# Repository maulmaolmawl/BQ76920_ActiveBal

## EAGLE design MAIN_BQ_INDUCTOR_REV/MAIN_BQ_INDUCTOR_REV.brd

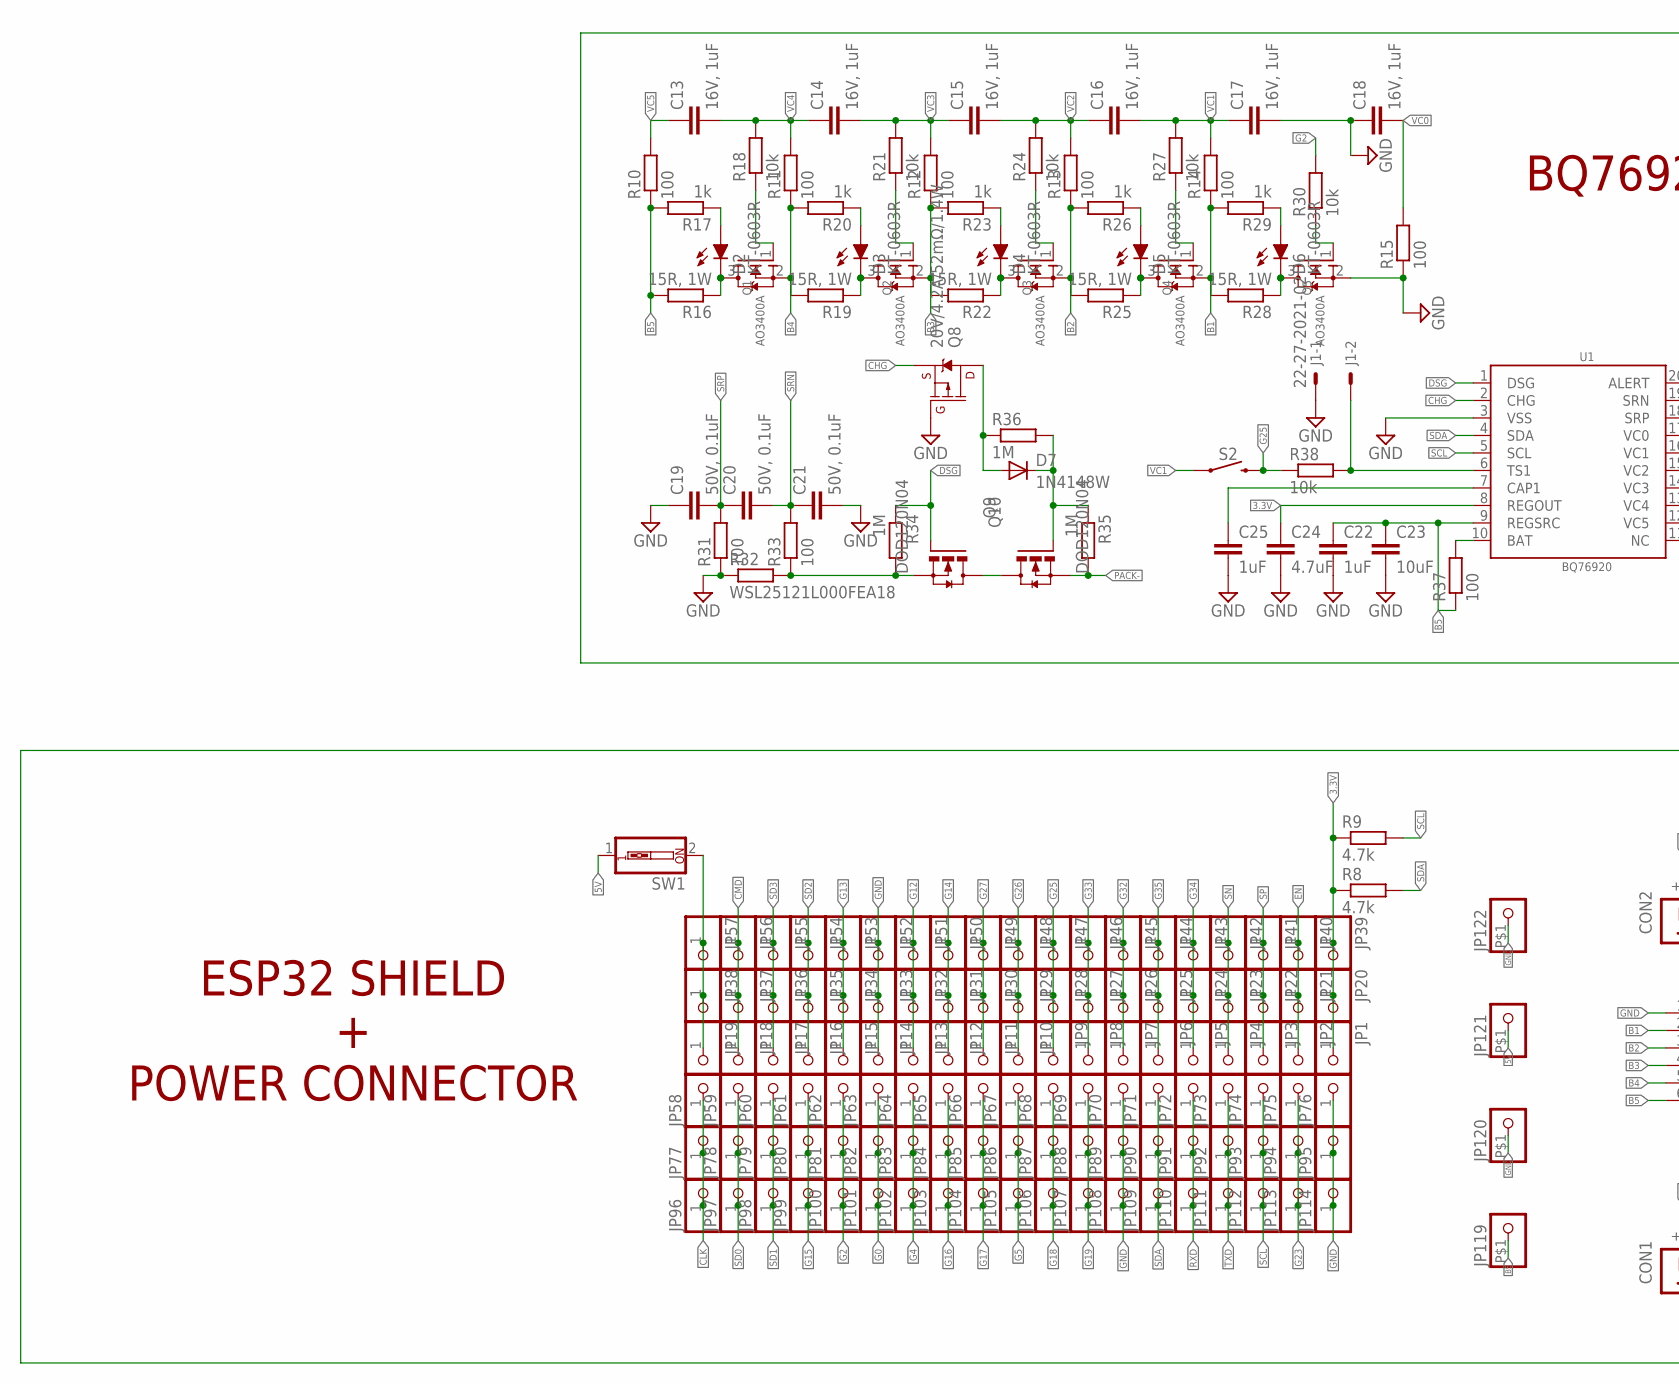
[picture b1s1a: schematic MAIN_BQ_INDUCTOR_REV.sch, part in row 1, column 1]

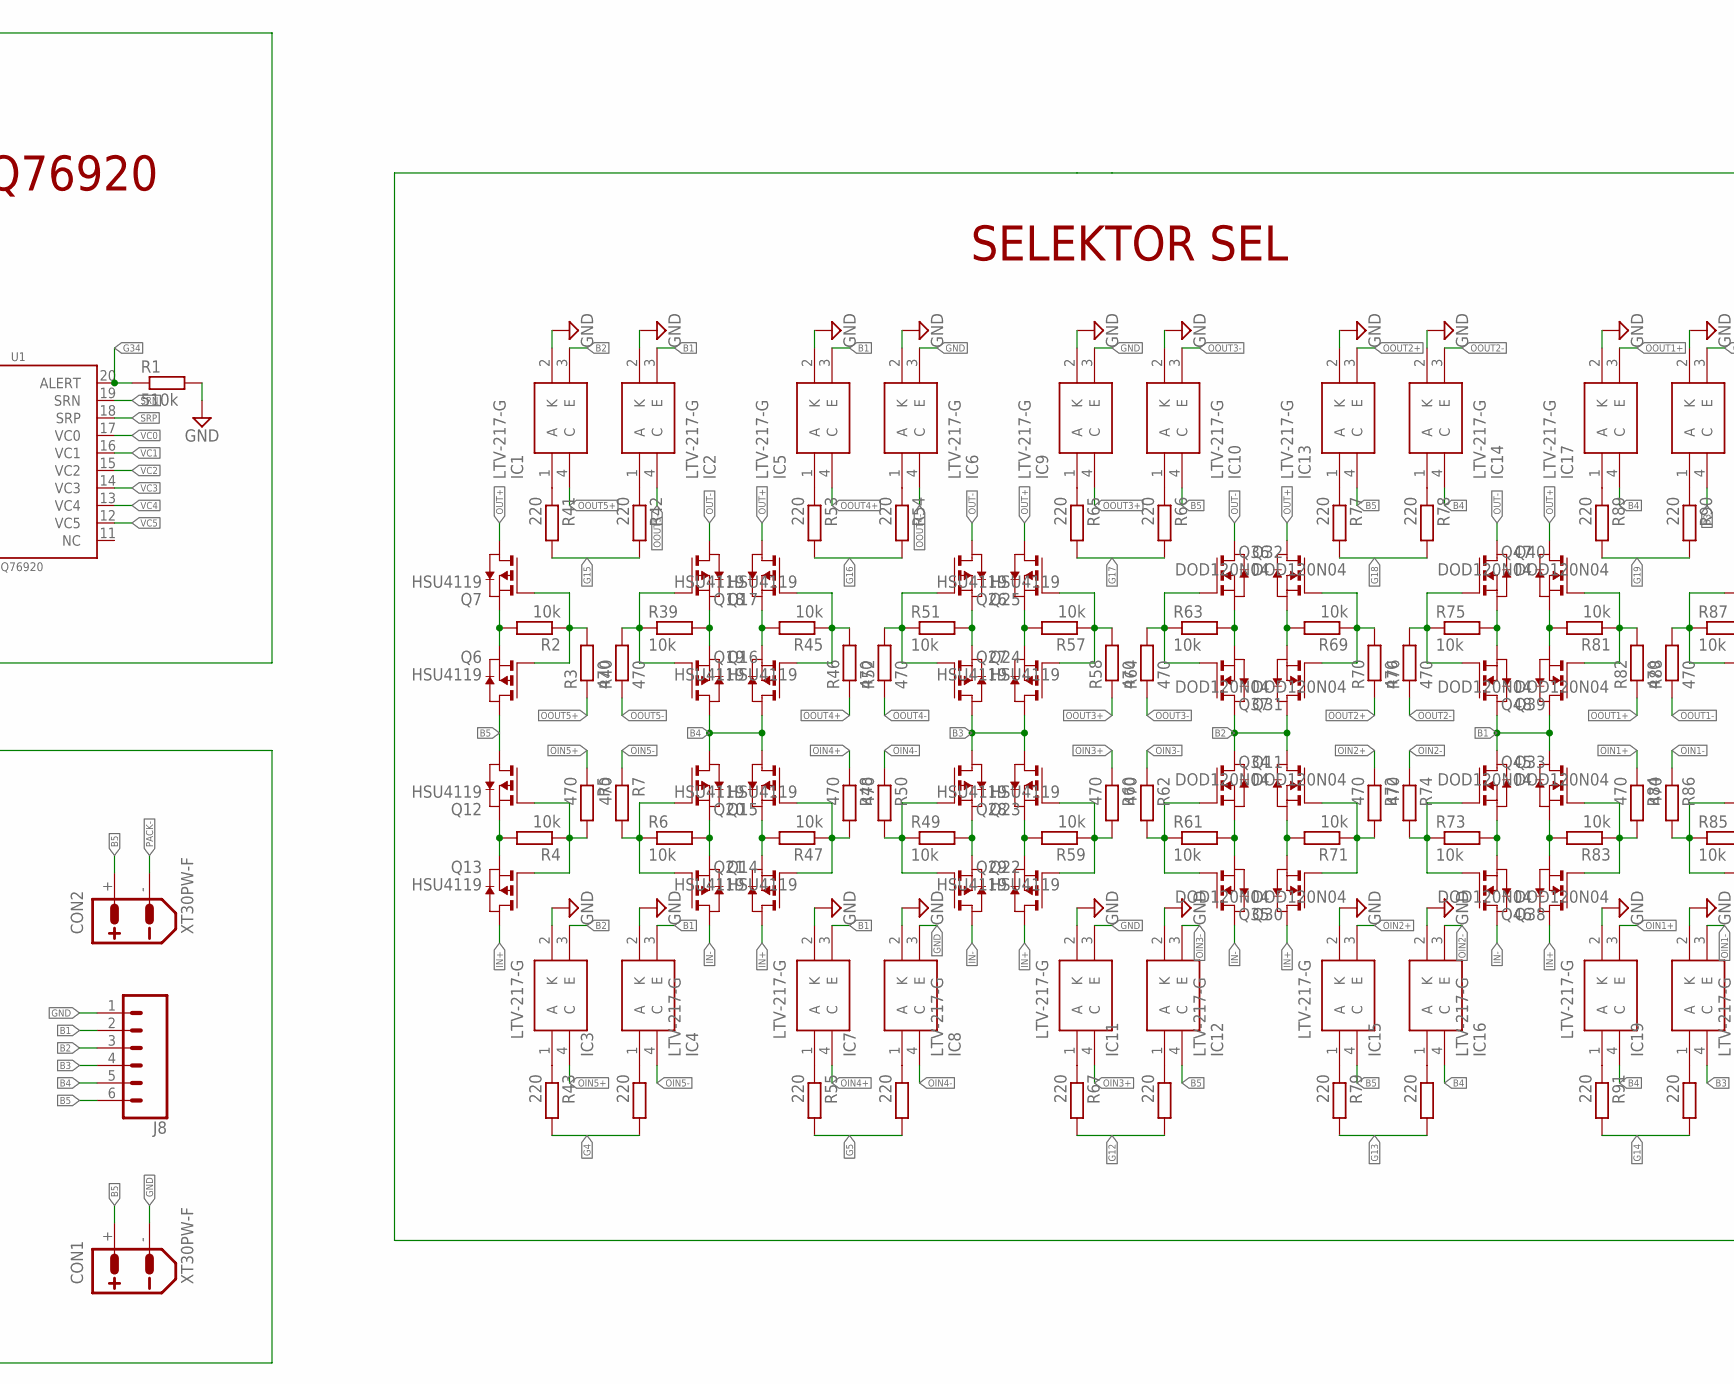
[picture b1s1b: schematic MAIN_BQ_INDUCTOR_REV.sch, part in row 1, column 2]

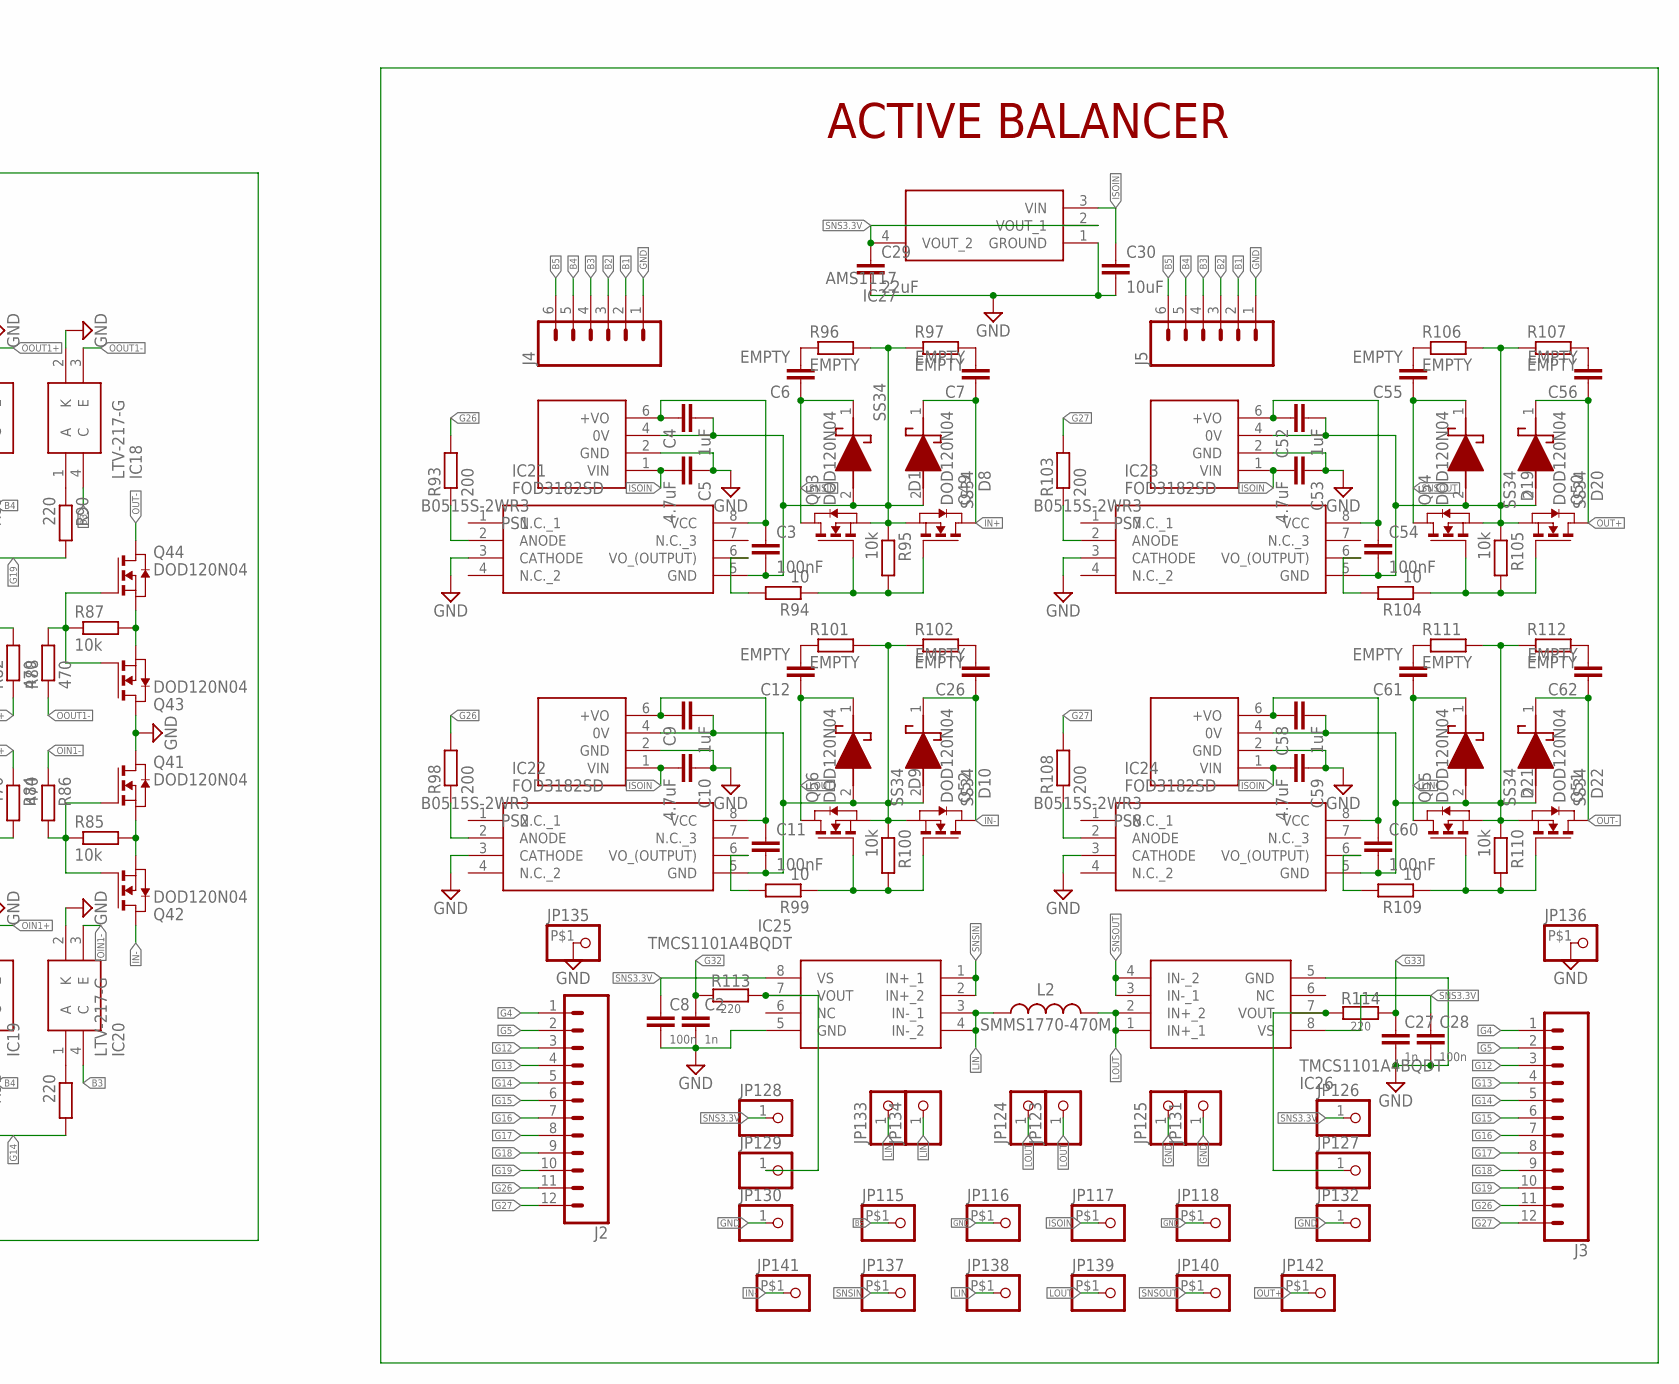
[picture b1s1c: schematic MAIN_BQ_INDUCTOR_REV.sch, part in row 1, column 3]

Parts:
C2, C27: 1n; C0805
C3, C11, C54, C60: 100nF; C0805
C4, C9, C52, C58: 1uF; C1206
C5, C10, C53, C59: 4.7uF; C1206
C6, C7, C12, C26, C55, C56, C61, C62: EMPTY; C1206
C8, C28: 100n; C0805
C13, C14, C15, C16, C17, C18: 16V, 1uF; C0805
C19, C20, C21: 50V, 0.1uF; C0603
C22, C25: 1uF; C0805
C23: 10uF; C1206
C24: 4.7uF; C0805
C29: 22uF; C0805
C30: 10uF; C0805
CON1, CON2: XT30PW-F
D1, D8, D9, D10, D19, D20, D21, D22: SS34; DIOM6959X262N
D2, D3, D4, D5, D6: KT-0603R; LED_CHIP-LED0603MP
D7: 1N4148W; SOD-123
IC1, IC2, IC3, IC4, IC5, IC6, IC7, IC8, IC9, IC10, IC11, IC12, IC13, IC14, IC15, IC16, IC17, IC18, IC19, IC20: LTV-217-G; LTV217G
IC21, IC22, IC23, IC24: FOD3182SD; SOP254P1000X400-8N
IC25, IC26: TMCS1101A4BQDT; SOIC127P600X175-8N
IC27: AMS1117; SOT229P700X180-4N
J1: 22-27-2021-02; 6410-02
J2, J3: CONN_12; 1X12
J4, J5, J8: CONN_06LONGPADS; 1X06_LONGPADS
JP1, JP2, JP3, JP4, JP5, JP6, JP7, JP8, JP9, JP10, JP11, JP12, JP13, JP14, JP15, JP16, JP17, JP18, JP19, JP20, JP21, JP22, JP23, JP24, JP25, JP26, JP27, JP28, JP29, JP30, JP31, JP32, JP33, JP34, JP35, JP36, JP37, JP38, JP39, JP40, JP41, JP42, JP43, JP44, JP45, JP46, JP47, JP48, JP49, JP50, JP51, JP52, JP53, JP54, JP55, JP56, JP57, JP58, JP59, JP60, JP61, JP62, JP63, JP64, JP65, JP66, JP67, JP68, JP69, JP70, JP71, JP72, JP73, JP74, JP75, JP76, JP77, JP78, JP79, JP80, JP81, JP82, JP83, JP84, JP85, JP86, JP87, JP88, JP89, JP90, JP91, JP92, JP93, JP94, JP95, JP96, JP97, JP98, JP99, JP100, JP101, JP102, JP103, JP104, JP105, JP106, JP107, JP108, JP109, JP110, JP111, JP112, JP113, JP114, JP123, JP124, JP125, JP126, JP127, JP128, JP129, JP130, JP131, JP132, JP133, JP134: PINHD-1X1; 1X01
JP115, JP116, JP117, JP118, JP119, JP120, JP121, JP122, JP135, JP136, JP137, JP138, JP139, JP140, JP141, JP142: PINHD-1X1-BIGPOGO; 1X1-BIGPOGO
L2: SMMS1770-470M; PA4344-17X17
PS1, PS2, PS7, PS8: B0515S-2WR3; B1212S2WR3
Q1, Q2, Q3, Q4, Q5: AO3400A; SOT23
Q6, Q7, Q12, Q13, Q14, Q15, Q16, Q17, Q18, Q19, Q20, Q21, Q22, Q23, Q24, Q25, Q26, Q27, Q28, Q29: HSU4119; TO252
Q8: 20V/4.2A/52mΩ/1.4W; SOT23-3
Q9, Q10: DOD120N04; DPAK
Q11, Q30, Q31, Q32, Q33, Q34, Q35, Q36, Q37, Q38, Q39, Q40, Q41, Q42, Q43, Q44, Q45, Q46, Q47, Q48, Q49, Q50, Q51, Q52, Q53, Q54, Q55, Q56: DOD120N04; TO252
R1: 510k; R0603
R2, R4, R6, R39, R45, R47, R49, R51, R57, R59, R61, R63, R69, R71, R73, R75, R81, R83, R85, R87, R95, R100, R105, R110: 10k; R0805
R3, R5, R7, R40, R46, R48, R50, R52, R58, R60, R62, R64, R70, R72, R74, R76, R82, R84, R86, R88: 470; R0805
R8, R9: 4.7k; R0402
R10, R11, R12, R13, R14, R15, R37: 100; R1206
R16, R19, R22, R25, R28: 15R, 1W; R2512
R17, R20, R23, R26, R29: 1k; R0402
R18, R21, R24, R27, R30, R38: 10k; R0402
R31, R33: 100; R0805
R32: WSL25121L000FEA18; R2512
R34, R35, R36: 1M; R0805
R41, R42, R43, R44, R53, R54, R55, R56, R65, R66, R67, R68, R77, R78, R79, R80, R89, R90, R91, R92, R113, R114: 220; R0805
R93, R98, R103, R108: 200; R0805
R94, R99, R104, R109: 10; R1206
R96, R97, R101, R102, R106, R107, R111, R112: EMPTY; R1206
S2: MOMENTARY-SWITCH-SPST-SMD-5.2-TALL-REDUNDANT; TACTILE_SWITCH_SMD_5.2MM
SW1: SW_DIP-1; EDG-01
U1: BQ76920; TSSOP-20_4.4X6.5MM_PITCH0.65MM

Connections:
3.3V: C24.1, JP1.1, JP20.1, JP39.1, R8.1, R9.1, U1.8 (REGOUT)
5V: JP121.P$1, SW1.1
B1: IC2.3 (E), IC4.3 (E), IC5.3 (E), IC7.3 (E), J4.2, J5.2, J8.2, Q4.2 (S), Q33.D, Q39.D, Q45.D, Q48.D, R14.1, R28.2, R29.2
B2: IC1.3 (E), IC3.3 (E), J4.3, J5.3, J8.3, Q3.2 (S), Q11.D, Q31.D, Q34.D, Q37.D, R13.1, R25.2, R26.2
B3: IC18.4 (C), IC20.4 (C), J4.4, J5.4, J8.4, Q2.2 (S), Q23.D, Q24.D, Q27.D, Q28.D, R12.1, R22.2, R23.2
B4: IC14.4 (C), IC16.4 (C), IC17.4 (C), IC19.4 (C), J4.5, J5.5, J8.5, Q1.2 (S), Q15.D, Q16.D, Q19.D, Q20.D, R11.1, R19.2, R20.2
B5: C22.1, C23.1, CON1.+, CON2.+, IC10.4 (C), IC12.4 (C), IC13.4 (C), IC15.4 (C), J4.6, J5.6, J8.6, JP115.P$1, JP119.P$1, Q6.D, Q12.D, R10.1, R16.2, R17.2, R37.1, U1.9 (REGSRC)
CHG: Q8.2 (S), U1.2 (CHG)
CLK: JP58.1, JP77.1, JP96.1
CMD: JP18.1, JP37.1, JP56.1
DSG: Q9.1 (G), R34.1, U1.1 (DSG)
EN: JP2.1, JP21.1, JP40.1
G0: JP63.1, JP82.1, JP101.1
G2: JP62.1, JP81.1, JP100.1, R30.2
G4: J2.1, J3.1, JP64.1, JP83.1, JP102.1, R43.2, R44.2
G5: J2.2, J3.2, JP67.1, JP86.1, JP105.1, R55.2, R56.2
G12: J2.3, J3.3, JP13.1, JP32.1, JP51.1, R67.2, R68.2
G13: J2.4, J3.4, JP15.1, JP34.1, JP53.1, R79.2, R80.2
G14: J2.5, J3.5, JP12.1, JP31.1, JP50.1, R91.2, R92.2
G15: J2.6, J3.6, JP61.1, JP80.1, JP99.1, R41.2, R42.2
G16: J2.7, J3.7, JP65.1, JP84.1, JP103.1, R53.2, R54.2
G17: J2.8, J3.8, JP66.1, JP85.1, JP104.1, R65.2, R66.2
G18: J2.9, J3.9, JP68.1, JP87.1, JP106.1, R77.2, R78.2
G19: J2.10, J3.10, JP69.1, JP88.1, JP107.1, R89.2, R90.2
G23: JP75.1, JP94.1, JP113.1
G25: JP9.1, JP28.1, JP47.1, R38.1, S2.3 (2), S2.4 (2)
G26: J2.11, J3.11, JP10.1, JP29.1, JP48.1, R93.2, R98.2
G27: J2.12, J3.12, JP11.1, JP30.1, JP49.1, R103.2, R108.2
G32: C2.1, JP7.1, JP26.1, JP45.1, R113.1
G33: C27.1, JP8.1, JP27.1, JP46.1, R114.2
G34: JP5.1, JP24.1, JP43.1, R1.1, U1.20 (ALERT)
G35: JP6.1, JP25.1, JP44.1
GND: C2.2, C5.1, C8.2, C10.1, C17.2, C18.1, C19.1, C21.2, C22.2, C23.2, C24.2, C25.2, C27.2, C28.2, C29.2, C30.2, C53.1, C59.1, CON1.-, IC1.2 (K), IC2.2 (K), IC3.2 (K), IC4.2 (K), IC5.2 (K), IC6.2 (K), IC6.3 (E), IC7.2 (K), IC8.2 (K), IC8.3 (E), IC9.2 (K), IC9.3 (E), IC10.2 (K), IC11.2 (K), IC11.3 (E), IC12.2 (K), IC13.2 (K), IC14.2 (K), IC15.2 (K), IC16.2 (K), IC17.2 (K), IC18.2 (K), IC19.2 (K), IC20.2 (K), IC21.3 (CATHODE), IC22.3 (CATHODE), IC23.3 (CATHODE), IC24.3 (CATHODE), IC25.5 (GND), IC26.5 (GND), IC27.1 (GROUND), J1.1, J4.1, J5.1, J8.1, JP14.1, JP33.1, JP52.1, JP70.1, JP76.1, JP89.1, JP95.1, JP108.1, JP114.1, JP116.P$1, JP118.P$1, JP120.P$1, JP122.P$1, JP125.1, JP130.1, JP131.1, JP132.1, JP135.P$1, JP136.P$1, PS1.2 (GND), PS2.2 (GND), PS7.2 (GND), PS8.2 (GND), Q5.2 (S), Q8.1 (G), Q41.D, Q43.D, R1.2, R15.1, R31.1, R32.1, U1.3 (VSS)
IN+: C7.1, D8.1 (K), Q13.D, Q21.D, Q29.D, Q35.D, Q46.D, Q49.D
IN-: C26.1, D10.1 (K), JP141.P$1, Q14.D, Q22.D, Q30.D, Q38.D, Q42.D, Q52.D
ISOIN: C5.2, C10.2, C30.1, C53.2, C59.2, IC27.3 (VIN), JP117.P$1, PS1.1 (VIN), PS2.1 (VIN), PS7.1 (VIN), PS8.1 (VIN)
LIN: C61.1, D21.1 (K), IC25.3 (IN-_1), IC25.4 (IN-_2), JP133.1, JP134.1, JP138.P$1, L2.1, Q55.D
LOUT: C12.1, D9.1 (K), IC26.1 (IN+_1), IC26.2 (IN+_2), JP123.1, JP124.1, JP139.P$1, L2.2, Q56.D
unnamed: Q12.G, Q13.G, R4.1, R5.2
unnamed: Q6.G, Q7.G, R2.1, R3.2
unnamed: Q12.S, Q13.S, R4.2
unnamed: Q6.S, Q7.S, R2.2
unnamed: Q26.G, Q27.G, R57.1, R58.2
unnamed: Q14.G, Q15.G, R6.1, R7.2
unnamed: Q14.S, Q15.S, R6.2
unnamed: Q16.G, Q17.G, R39.1, R40.2
unnamed: Q16.S, Q17.S, R39.2
unnamed: Q26.S, Q27.S, R57.2
unnamed: IC21.6 (VO_(OUTPUT)), R94.2
unnamed: JP19.1, JP38.1, JP57.1, SW1.2
unnamed: D7.A, Q8.3 (D), R36.1
unnamed: Q9.3 (S), R32.2, R33.1, R34.2
unnamed: C3.1, C4.1, IC21.8 (VCC), PS1.6 (+VO)
unnamed: Q9.2 (D), Q10.2 (D)
unnamed: R37.2, U1.10 (BAT)
unnamed: IC21.2 (ANODE), R93.1
unnamed: C3.2, C4.2, D1.2 (A), D8.2 (A), IC21.5 (GND), PS1.4 (0V), Q49.S, Q53.S, R95.1, R96.2, R97.1
unnamed: Q49.G, Q53.G, R94.1, R95.2
unnamed: C6.2, R96.1
unnamed: IC1.1 (A), R41.1
unnamed: IC2.1 (A), R42.1
unnamed: C7.2, R97.2
unnamed: IC22.6 (VO_(OUTPUT)), R99.2
unnamed: D7.C, Q10.1 (G), R35.1, R36.2
unnamed: IC3.1 (A), R43.1
unnamed: C9.1, C11.1, IC22.8 (VCC), PS2.6 (+VO)
unnamed: IC4.1 (A), R44.1
unnamed: IC22.2 (ANODE), R98.1
unnamed: J1.2, R38.2, U1.6 (TS1)
unnamed: C25.1, U1.7 (CAP1)
unnamed: C9.2, C11.2, D9.2 (A), D10.2 (A), IC22.5 (GND), PS2.4 (0V), Q52.S, Q56.S, R100.1, R101.2, R102.1
unnamed: Q52.G, Q56.G, R99.1, R100.2
unnamed: Q18.G, Q19.G, R45.1, R46.2
unnamed: Q18.S, Q19.S, R45.2
unnamed: Q20.G, Q21.G, R47.1, R48.2
unnamed: Q20.S, Q21.S, R47.2
unnamed: Q28.G, Q29.G, R59.1, R60.2
unnamed: Q22.G, Q23.G, R49.1, R50.2
unnamed: Q22.S, Q23.S, R49.2
unnamed: D2.C, Q1.3 (D), R16.1
unnamed: D2.A, R17.1
unnamed: Q1.1 (G), R18.1
unnamed: D3.C, Q2.3 (D), R19.1
unnamed: D3.A, R20.1
unnamed: Q2.1 (G), R21.1
unnamed: D4.C, Q3.3 (D), R22.1
unnamed: D4.A, R23.1
unnamed: Q3.1 (G), R24.1
unnamed: D5.C, Q4.3 (D), R25.1
unnamed: D5.A, R26.1
unnamed: Q4.1 (G), R27.1
unnamed: D6.C, Q5.3 (D), R28.1
unnamed: D6.A, R29.1
unnamed: Q5.1 (G), R30.1
unnamed: Q24.G, Q25.G, R51.1, R52.2
unnamed: Q24.S, Q25.S, R51.2
unnamed: Q36.G, Q37.G, R69.1, R70.2
unnamed: C12.2, R101.1
unnamed: C26.2, R102.2
unnamed: IC5.1 (A), R53.1
unnamed: C52.1, C54.1, IC23.8 (VCC), PS7.6 (+VO)
unnamed: IC6.1 (A), R54.1
unnamed: IC23.2 (ANODE), R103.1
unnamed: IC7.1 (A), R55.1
unnamed: IC8.1 (A), R56.1
unnamed: Q50.G, Q54.G, R104.1, R105.2
unnamed: Q51.G, Q55.G, R109.1, R110.2
unnamed: C61.2, R111.1
unnamed: C62.2, R112.2
unnamed: IC25.7 (VOUT), JP129.1, R113.2
unnamed: IC26.7 (VOUT), JP127.1, R114.1
unnamed: Q28.S, Q29.S, R59.2
unnamed: Q36.S, Q37.S, R69.2
unnamed: Q11.G, Q30.G, R61.1, R62.2
unnamed: Q11.S, Q30.S, R61.2
unnamed: Q31.G, Q32.G, R63.1, R64.2
unnamed: Q31.S, Q32.S, R63.2
unnamed: Q47.G, Q48.G, R81.1, R82.2
unnamed: IC23.6 (VO_(OUTPUT)), R104.2
unnamed: IC9.1 (A), R65.1
unnamed: IC10.1 (A), R66.1
unnamed: C52.2, C54.2, D19.2 (A), D20.2 (A), IC23.5 (GND), PS7.4 (0V), Q50.S, Q54.S, R105.1, R106.2, R107.1
unnamed: IC11.1 (A), R67.1
unnamed: IC12.1 (A), R68.1
unnamed: C55.2, R106.1
unnamed: C56.2, R107.2
unnamed: IC24.6 (VO_(OUTPUT)), R109.2
unnamed: C58.1, C60.1, IC24.8 (VCC), PS8.6 (+VO)
unnamed: IC24.2 (ANODE), R108.1
unnamed: C58.2, C60.2, D21.2 (A), D22.2 (A), IC24.5 (GND), PS8.4 (0V), Q51.S, Q55.S, R110.1, R111.2, R112.1
unnamed: Q34.G, Q35.G, R71.1, R72.2
unnamed: Q34.S, Q35.S, R71.2
unnamed: Q33.G, Q38.G, R73.1, R74.2
unnamed: Q33.S, Q38.S, R73.2
unnamed: Q39.G, Q40.G, R75.1, R76.2
unnamed: Q39.S, Q40.S, R75.2
unnamed: IC13.1 (A), R77.1
unnamed: IC14.1 (A), R78.1
unnamed: IC15.1 (A), R79.1
unnamed: IC16.1 (A), R80.1
unnamed: Q47.S, Q48.S, R81.2
unnamed: Q45.G, Q46.G, R83.1, R84.2
unnamed: Q45.S, Q46.S, R83.2
unnamed: Q41.G, Q42.G, R85.1, R86.2
unnamed: Q41.S, Q42.S, R85.2
unnamed: Q43.G, Q44.G, R87.1, R88.2
unnamed: Q43.S, Q44.S, R87.2
unnamed: IC17.1 (A), R89.1
unnamed: IC18.1 (A), R90.1
unnamed: IC19.1 (A), R91.1
unnamed: IC20.1 (A), R92.1
OIN1+: IC19.3 (E), R84.1
OIN1-: IC20.3 (E), R86.1
OIN2+: IC15.3 (E), R72.1
OIN2-: IC16.3 (E), R74.1
OIN3+: IC11.4 (C), R60.1
OIN3-: IC12.3 (E), R62.1
OIN4+: IC7.4 (C), R48.1
OIN4-: IC8.4 (C), R50.1
OIN5+: IC3.4 (C), R5.1
OIN5-: IC4.4 (C), R7.1
OOUT1+: IC17.3 (E), R82.1
OOUT1-: IC18.3 (E), R88.1
OOUT2+: IC13.3 (E), R70.1
OOUT2-: IC14.3 (E), R76.1
OOUT3+: IC9.4 (C), R58.1
OOUT3-: IC10.3 (E), R64.1
OOUT4+: IC5.4 (C), R46.1
OOUT4-: IC6.4 (C), R52.1
OOUT5+: IC1.4 (C), R3.1
OOUT5-: IC2.4 (C), R40.1
OUT+: C56.1, D20.1 (K), JP142.P$1, Q7.D, Q18.D, Q26.D, Q36.D, Q47.D, Q50.D
OUT-: C62.1, D22.1 (K), Q17.D, Q25.D, Q32.D, Q40.D, Q44.D, Q51.D
PACK-: CON2.-, Q10.3 (S), R35.2
RXD: JP72.1, JP91.1, JP110.1
SCL: JP74.1, JP93.1, JP112.1, R9.2, U1.5 (SCL)
SD0: JP59.1, JP78.1, JP97.1
SD1: JP60.1, JP79.1, JP98.1
SD2: JP16.1, JP35.1, JP54.1
SD3: JP17.1, JP36.1, JP55.1
SDA: JP71.1, JP90.1, JP109.1, R8.2, U1.4 (SDA)
SN: JP4.1, JP23.1, JP42.1
SNS3.3V: C8.1, C28.1, C29.1, IC25.8 (VS), IC26.8 (VS), IC27.2 (VOUT_1), IC27.4 (VOUT_2), JP126.1, JP128.1
SNSIN: C6.1, D1.1 (K), IC25.1 (IN+_1), IC25.2 (IN+_2), JP137.P$1, Q53.D
SNSOUT: C55.1, D19.1 (K), IC26.3 (IN-_1), IC26.4 (IN-_2), JP140.P$1, Q54.D
SP: JP3.1, JP22.1, JP41.1
SRN: C20.2, C21.1, R33.2, U1.19 (SRN)
SRP: C19.2, C20.1, R31.2, U1.18 (SRP)
TXD: JP73.1, JP92.1, JP111.1
VC0: C18.2, R15.2, U1.17 (VC0)
VC1: C16.2, C17.1, R14.2, R27.2, S2.1, S2.2 (1), U1.16 (VC1)
VC2: C15.2, C16.1, R13.2, R24.2, U1.15 (VC2)
VC3: C14.2, C15.1, R12.2, R21.2, U1.14 (VC3)
VC4: C13.2, C14.1, R11.2, R18.2, U1.13 (VC4)
VC5: C13.1, R10.2, U1.12 (VC5)

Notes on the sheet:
ESP32 SHIELD + POWER CONNECTOR
BQ76920
SELEKTOR SEL
ACTIVE BALANCER

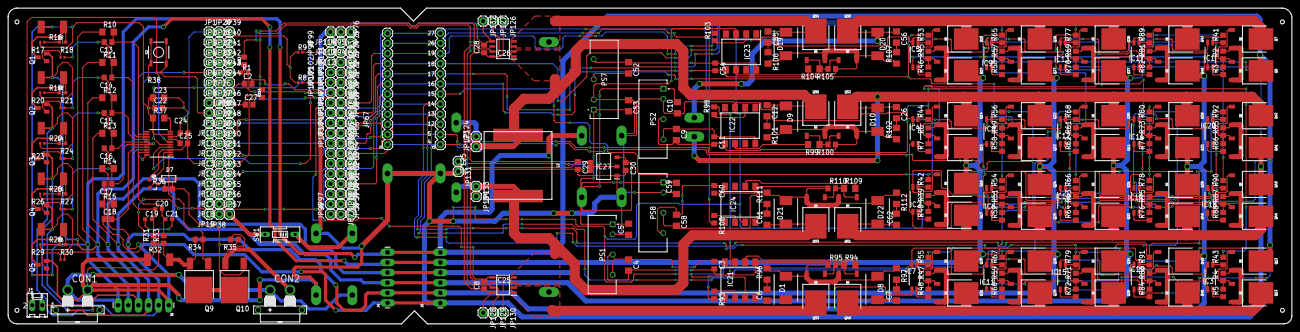
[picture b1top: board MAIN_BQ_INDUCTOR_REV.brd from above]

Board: 2 copper layers, 322.2 x 79.2 mm, 408 parts (1 on the bottom side), 195 nets.

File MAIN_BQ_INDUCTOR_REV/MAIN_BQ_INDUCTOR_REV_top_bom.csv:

Comment,Designator,Footprint,LCSC Part #
1M,R34 R35 R36,R0805,
1N4148W,D7,SOD-123,
1k,R17 R20 R23 R26 R29,R0402,
1n,C2 C27,C0805,
1uF,C4 C9,C1206,
1uF,C22 C25,C0805,
1uF,C52 C58,C1206,
4.7k,R8 R9,R0402,
4.7uF,C5 C10,C1206,
4.7uF,C24,C0805,
4.7uF,C53 C59,C1206,
10,R94 R99 R104 R109,R1206,
10k,R2 R4 R6,R0805,
10k,R18 R21 R24 R27 R30 R38,R0402,
10k,R39 R45 R47 R49 R51 R57 R59 R61 R63 R69 R71 R73 R75 R81 R83 R85 R87 R95 R100 R105 R110,R0805,
10uF,C23,C1206,
10uF,C30,C0805,
15R  1W,R16,R2512,
15R  1W,R19,R2512,
15R  1W,R22,R2512,
15R  1W,R25,R2512,
15R  1W,R28,R2512,
16V  1uF,C13,C0805,
16V  1uF,C14,C0805,
16V  1uF,C15,C0805,
16V  1uF,C16,C0805,
16V  1uF,C17,C0805,
16V  1uF,C18,C0805,
20V/4.2A/52mΩ/1.4W,Q8,SOT23-3,
22uF,C29,C0805,
50V  0.1uF,C19,C0603,
50V  0.1uF,C20,C0603,
50V  0.1uF,C21,C0603,
100,R10 R11 R12 R13 R14 R15,R1206,
100,R31 R33,R0805,
100,R37,R1206,
100n,C8 C28,C0805,
100nF,C3 C11 C54 C60,C0805,
200,R93 R98 R103 R108,R0805,
220,R41 R42 R43 R44 R53 R54 R55 R56 R65 R66 R67 R68 R77 R78 R79 R80 R89 R90 R91 R92 R113 R114,R0805,
470,R3 R5 R7 R40 R46 R48 R50 R52 R58 R60 R62 R64 R70 R72 R74 R76 R82 R84 R86 R88,R0805,
510k,R1,R0603,
AMS1117,IC27,SOT229P700X180-4N,
AO3400A,Q1 Q2 Q3 Q4 Q5,SOT23,
BQ76920,U1,TSSOP-20_4.4X6.5MM_PITCH0.65MM,
DOD120N04,Q9 Q10,DPAK,
DOD120N04,Q11 Q30 Q31 Q32 Q33 Q34 Q35 Q36 Q37 Q38 Q39 Q40 Q41 Q42 Q43 Q44 Q45 Q46 Q47 Q48 Q49 Q50 Q51 Q52 Q53 Q54 Q55 Q56,TO252,
EMPTY,C6 C7 C12 C26 C55 C56 C61 C62,C1206,
EMPTY,R96 R97 R101 R102 R106 R107 R111 R112,R1206,
HSU4119,Q6 Q7 Q12 Q13 Q14 Q15 Q16 Q17 Q18 Q19 Q20 Q21 Q22 Q23 Q24 Q25 Q26 Q27 Q28 Q29,TO252,
KT-0603R,D2 D3 D4 D5 D6,LED_CHIP-LED0603MP,
LTV-217-G,IC1 IC2 IC3 IC4 IC5 IC6 IC7 IC8 IC9 IC10 IC11 IC12 IC13 IC14 IC15 IC16 IC17 IC18 IC19 IC20,LTV217G,
MOMENTARY-SWITCH-SPST-SMD-5.2-TALL-REDUNDANT,S2,TACTILE_SWITCH_SMD_5.2MM,
SMMS1770-470M,L2,PA4344-17X17,
SS34,D1 D8 D9 D10 D19 D20 D21 D22,DIOM6959X262N,
TLP350(TP1 F),IC21,SOP254P1000X400-8N,
TLP350(TP1 F),IC22,SOP254P1000X400-8N,
TLP350(TP1 F),IC23,SOP254P1000X400-8N,
TLP350(TP1 F),IC24,SOP254P1000X400-8N,
TMCS1101A4BQDT,IC25 IC26,SOIC127P600X175-8N,
WSL25121L000FEA18,R32,R2512,
B0515S-2WR3,PS1 PS2 PS7 PS8,"SIP,19.5?7mm",

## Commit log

2026-06-24 Create Code

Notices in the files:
parts and their libraries:
SparkFun-DiscreteSemi: Licensing: Creative Commons ShareAlike 4.0 International - https://creativecommons.org/licenses/by-sa/4.0
